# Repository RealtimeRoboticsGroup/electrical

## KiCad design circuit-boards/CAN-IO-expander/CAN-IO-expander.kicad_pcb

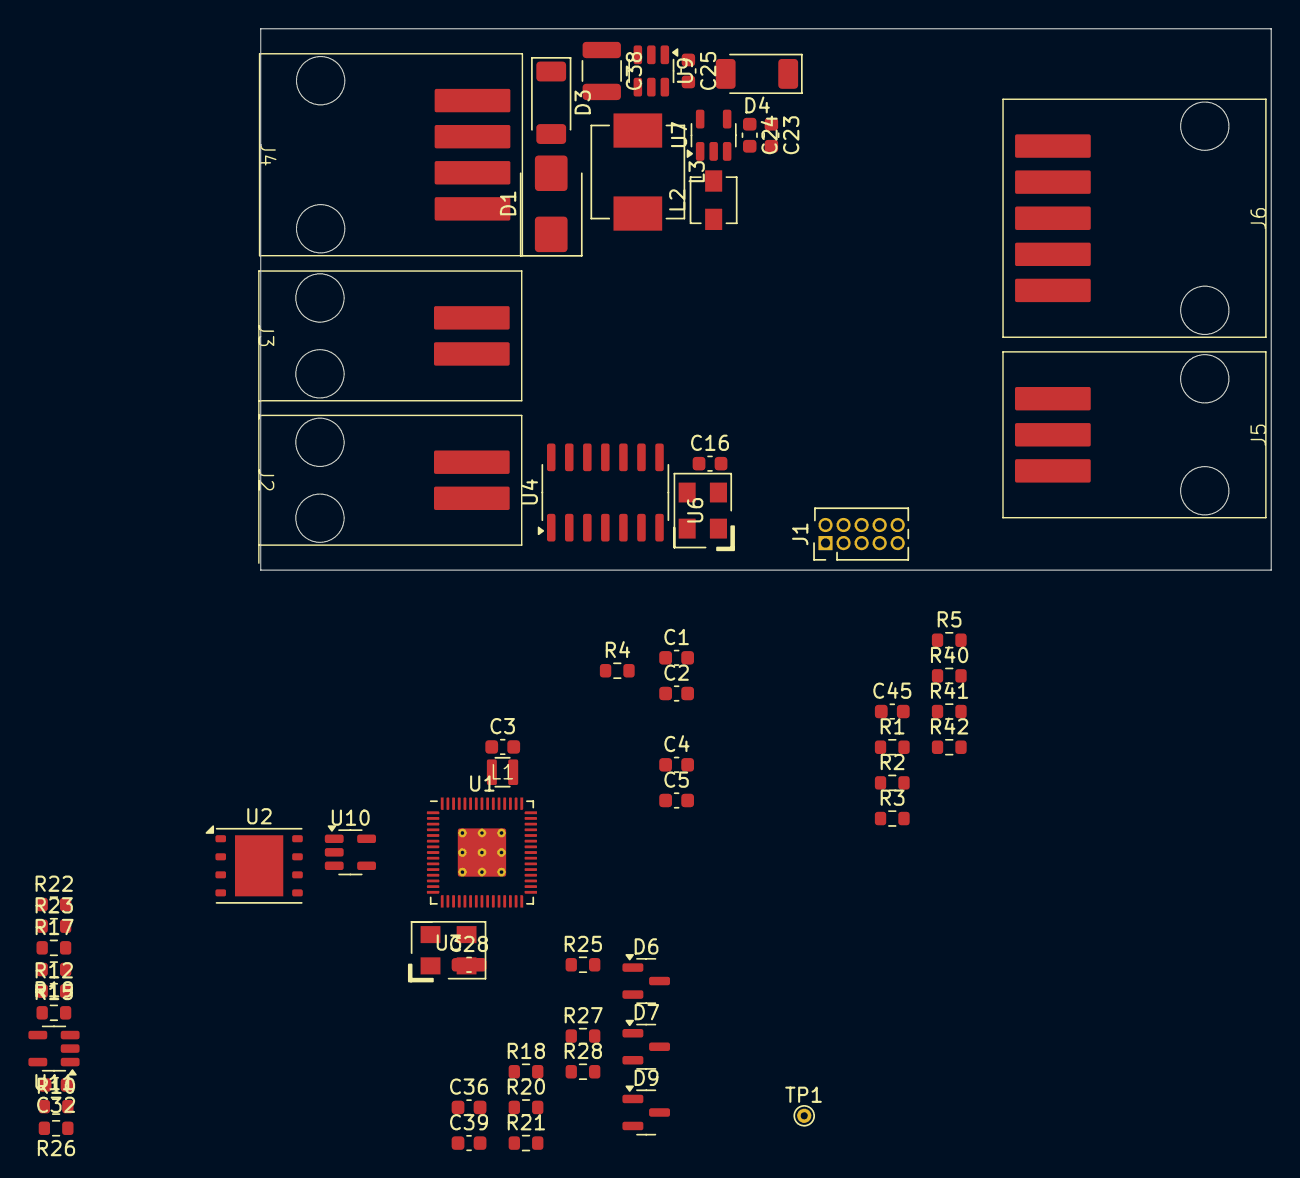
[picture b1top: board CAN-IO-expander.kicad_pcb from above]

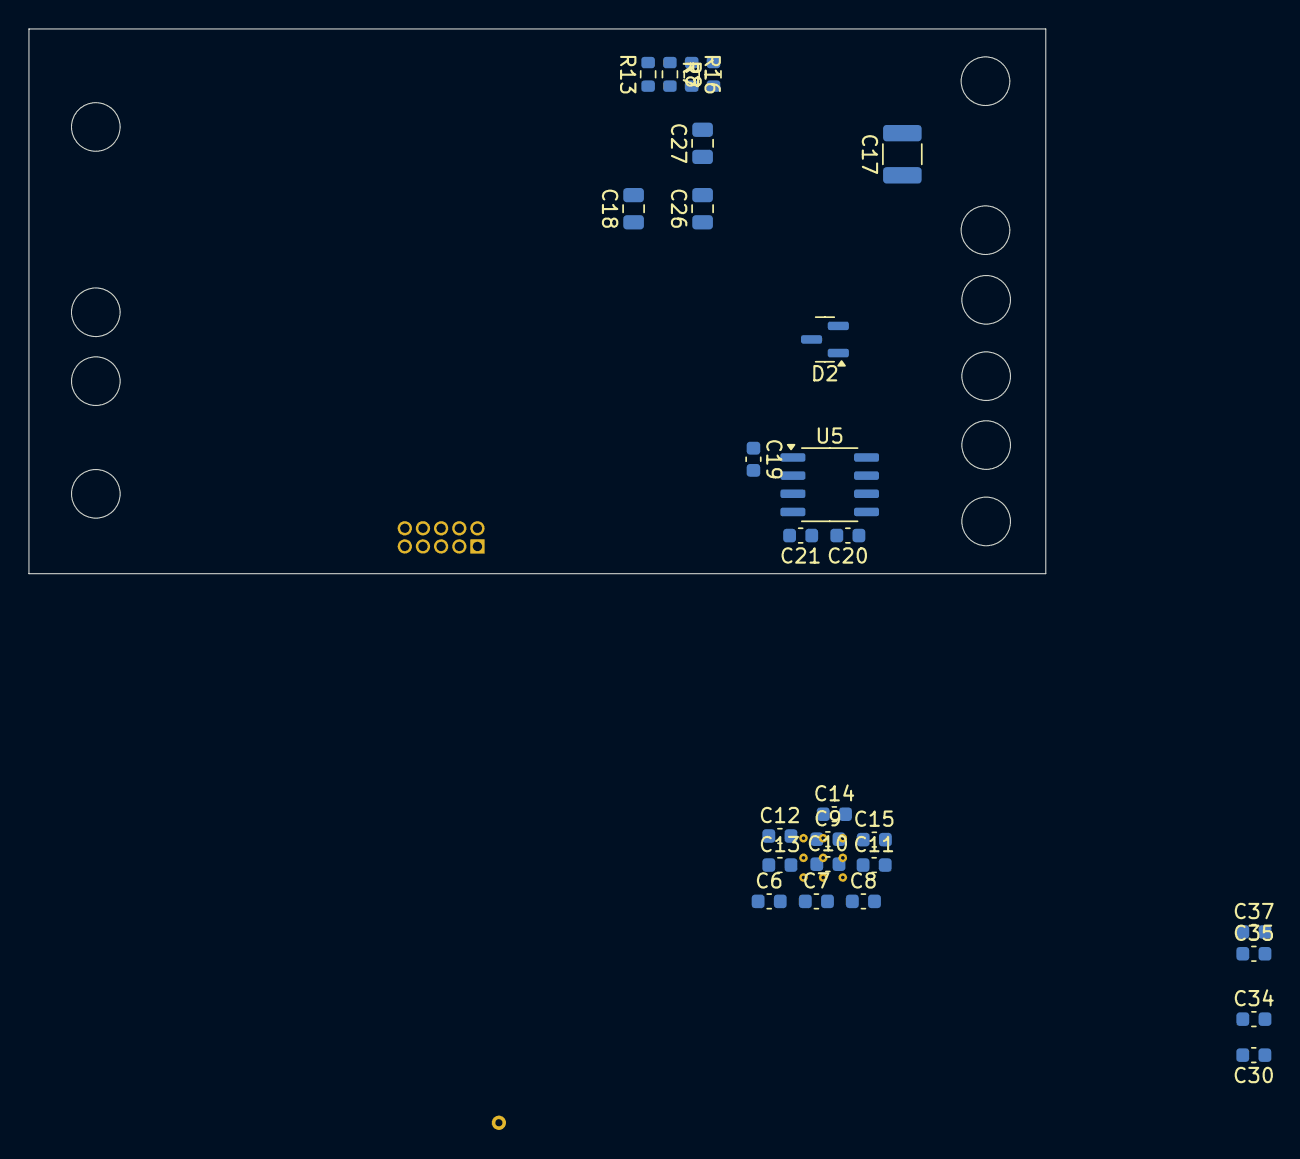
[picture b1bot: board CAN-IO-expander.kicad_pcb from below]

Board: 2 copper layers, 71.1 x 38.1 mm, 89 parts (27 on the bottom side), 63 nets, no tracks yet.

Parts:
C1, C2, C7, C8, C9, C10, C11, C12, C13, C14, C15, C16, C19, C20, C21, C25, C30, C45: 0.1uF-25V-10%-0603; C_0603_1608Metric
C3, C4, C5, C6: 4.7uF-16V-10%-0603; C_0603_1608Metric
C17, C38: 22uF-25V-10%-1210; C_1210_3225Metric
C18, C26, C27: 10uF-10%-10V-0805; C_0805_2012Metric
C23, C24: 22uF-20%-0603; C_0603_1608Metric
C28, C32, C34, C35, C36, C37, C39: 1nF-50V-5%-0603; C_0603_1608Metric
D1: 15V; D_SMB
D2: PESD1CAN; SOT-23
D3, D4: PMEG3020EP,115; D_SOD-128
D6, D7, D9: BAV199; SOT-23
J1: PROG; PinHeader_2x05_P1.27mm_Vertical
J2, J3: CAN1; Molex-70634-0036
J4: 12V; Molex-70634-0038
J5: POT; Molex-70634-0037
J6: ENCODER; Molex-70634-0039
L1: 3.3uH-20%-0806; L_Taiyo_Yuden_0806
L2: 2.2uH-20%-46mR; L_Vishay_IHLP-1212
L3: 8.2uH-20%-55mR; L_Vishay_IHLP-2525
R1, R5, R10, R12, R18, R20, R21: 1.00k-1%-0603; R_0603_1608Metric
R2, R3, R4: 27R0-1%-0603; R_0603_1608Metric
R7: 63.4k-1%-0603; R_0603_1608Metric
R8, R13: 20.0k-1%-0603; R_0603_1608Metric
R15, R17, R19, R23, R40, R41, R42: 2.00k-1%-0603; R_0603_1608Metric
R16, R22: 10.0k-1%-0603; R_0603_1608Metric
R25, R27, R28: 100R-1%-0603; R_0603_1608Metric
R26: 1.00M-1%-0603; R_0603_1608Metric
TP1: CLKO; TestPoint_THTPad_D1.0mm_Drill0.5mm
U1: RP2350_60QFN; RP2350-QFN-60-1EP_7x7_P0.4mm_EP3.4x3.4mm_ThermalVias
U2: W25Q128JVP; WSON-8-1EP_6x5mm_P1.27mm_EP3.4x4.3mm
U3: 12MHz; ECS-5032MV
U4: MCP2518FDT-H/SL; SO-14_3.9x8.65mm_P1.27mm
U5: MCP2558FD; SO-8_3.9x4.9mm_P1.27mm
U6: 4MHz; ECS-5032MV
U7: TPS613222ADBVR; SOT-23-5
U9: LMR54410FDBVR; SOT-23-6
U10: 24LC01BT-I/OT; SOT-23-5
U11: MCP6006UT-E/OT; SOT-23-5

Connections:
+1V1: C3.1, C6.1, C7.1, C8.1, L1.1, U1.6 (DVDD), U1.23 (DVDD), U1.39 (DVDD), U1.50 (VREG_FB)
+3V3: C1.1, C2.1, C4.1, C16.1, C18.1, C19.1, C20.1, C26.1, C27.1, C45.1, D6.2 (A), D7.2 (A), D9.2 (A), L2.1, L3.2, R2.1, R7.2, R40.2, R41.2, R42.2, U1.49 (VREG_VIN), U2.8 (VCC), U3.1 (EN), U3.4 (V_{DD}), U4.14 (VDD), U5.5 (V_{IO}), U6.1 (EN), U6.4 (V_{DD}), U10.4 (Vcc)
+5V: C21.1, C23.1, C24.1, C30.1, D4.2 (A), U5.3 (V_{DD}), U7.4 (VOUT), U11.5 (V+)
+5V_EXT: D4.1 (K), J5.2, J6.4, R19.2
/5V_ADC: C35.1, R17.2, R19.1, U1.42 (GPIO28_ADC2)
/AIN0: J5.3, R10.1, R26.2
/AIN0_ADC: C34.1, R12.2, R15.2, U1.40 (GPIO26_ADC0)
/CAN1_H: D2.2 (K1), J2.2, J3.2, U5.7 (CANH)
/CAN1_L: D2.1 (K1), J2.1, J3.1, U5.6 (CANL)
/CAN-FD/CANRX: U4.2 (RXCAN), U5.4 (RXD)
/CAN-FD/CANTX: U4.1 (TXCAN), U5.1 (TXD)
/CAN-FD/CLK: U4.6 (OSC1), U6.3 (OUT)
/DI00: D6.3 (K), R21.2, U1.18 (GPIO14)
/DI10: D7.3 (K), R20.2, U1.16 (GPIO12)
/DI20: D9.3 (K), R18.2, U1.19 (GPIO15), U1.28 (GPIO17)
/EEPROM_WP: R42.1, U1.14 (GPIO10), U10.5 (WP)
/I2C0_SCL: R40.1, U1.13 (GPIO9), U10.1 (SCL)
/I2C0_SDA: R41.1, U1.12 (GPIO8), U10.3 (SDA)
/PWM_IN0: J6.1, R25.1
/QA0: J6.3, R28.1
/QB0: J6.2, R27.1
/QSPI_D0: U1.57 (QSPI_SD0), U2.5 (DI/IO_{0})
/QSPI_D1: U1.59 (QSPI_SD1), U2.2 (DO/IO_{1})
/QSPI_D2: U1.58 (QSPI_SD2), U2.3 (~WP/IO_{2})
/QSPI_D3: U1.55 (QSPI_SD3), U2.7 (~HOLD/~RESET/IO_{3})
/QSPI_SCLK: U1.56 (QSPI_SCLK), U2.6 (CLK)
/SILENT: U1.10 (GPIO7), U5.8 (S)
/SPI0_RX: U1.2 (GPIO0), U4.12 (SDO)
/SPI0_SCK: U1.4 (GPIO2), U4.10 (SCK)
/SPI0_TX: U1.5 (GPIO3), U4.11 (SDI)
/SWCLK: J1.4, U1.24 (SWCLK)
/SWD: J1.6, U1.25 (SWD)
/USB_D+: J1.2, R3.2
/USB_D-: J1.1, R4.2
/VBAT_ADC: C37.1, R22.2, R23.2, U1.43 (GPIO29_ADC3)
/VREG_LX: L1.2, U1.48 (VREG_LX)
/V_{BAT}: C17.2, D1.2 (A2), D3.2 (A), J4.3, J4.4
/~CAN_INT: U1.7 (GPIO4), U4.4 (~INT)
/~CAN_RX_INT: U1.8 (GPIO5), U4.9 (~INT0/GPIO0/XSTBY)
/~CAN_TX_INT: U1.9 (GPIO6), U4.8 (~INT1/GPIO1)
/~QSPI_SS: R1.2, U1.60 (QSPI_SS), U2.1 (~CS)
/~RESET: J1.10, R5.1
/~SPI0_CS: U1.3 (GPIO1), U4.13 (~CS)
/~USB_BOOT: J1.8, R1.1
GND: C1.2, C2.2, C3.2, C4.2, C5.2, C6.2, C7.2, C8.2, C9.2, C10.2, C11.2, C12.2, C13.2, C14.2, C15.2, C16.2, C17.1, C18.2, C19.2, C20.2, C21.2, C23.2, C24.2, C26.2, C27.2, C28.2, C30.2, C32.2, C34.2, C35.2, C36.2, C37.2, C38.1, C39.2, C45.2, D1.1 (A1), D2.3 (KK), D6.1 (K), D7.1 (K), D9.1 (K), J1.5, J1.7, J1.9, J4.1, J4.2, J5.1, J6.5, R13.1, R15.1, R16.1, R17.1, R23.1, R26.1, U1.47 (VREG_PGND), U1.61 (GND), U2.4 (GND), U2.9 (EP), U3.2 (GND), U4.7 (VSS), U5.2 (V_{SS}), U6.2 (GND), U7.2 (GND), U7.3 (NC), U7.5 (NC), U9.2 (GND), U10.2 (Vss), U11.2 (V-)
unnamed: C28.1, R21.1, R28.2
unnamed: C36.1, R20.1, R27.2
unnamed: C39.1, R18.1, R25.2
unnamed: C38.2, D3.1 (K), R8.2, R22.1, U9.5 (VIN)
unnamed: C9.1, C10.1, C11.1, C12.1, C13.1, C14.1, C15.1, U1.1 (IOVDD), U1.11 (IOVDD), U1.20 (IOVDD), U1.30 (IOVDD), U1.38 (IOVDD), U1.44 (ADC_AVDD), U1.45 (IOVDD), U1.53 (USB_OTP_VDD), U1.54 (QSPI_IOVDD)
unnamed: R5.2, U1.26 (RUN)
unnamed: R4.1, U1.51 (USB_DM)
unnamed: R3.1, U1.52 (USB_DP)
unnamed: C5.1, R2.2, U1.46 (VREG_AVDD)
unnamed: U1.21 (XIN), U3.3 (OUT)
unnamed: TP1.1, U4.3 (CLKO/SOF)
unnamed: L2.2, U7.1 (SW)
unnamed: C25.1, U9.1 (CB)
unnamed: R8.1, R16.2, U9.4 (EN)
unnamed: R7.1, R13.2, U9.3 (FB)
unnamed: C25.2, L3.1, U9.6 (SW)
unnamed: C32.1, R10.2, U11.3 (+)
unnamed: R12.1, U11.1, U11.4 (-)

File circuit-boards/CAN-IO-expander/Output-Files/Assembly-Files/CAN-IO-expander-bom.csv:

"Reference","Value","DIST","DIST P/N","MFG","MFG P/N","Item","QUANTITY"
"C1,C2,C7-C16,C19-C21,C28-C37,C39-C45,J4-J7,R1-R5,R10-R12,R14,R15,R17-R21,R23-R42","0.1uF-25V-10%-0603,1.00M-1%-0603,1.00k-1%-0603,100R-1%-0603,1nF-50V-5%-0603,2.00k-1%-0603,27R0-1%-0603,Conn_01x03_Pin,Conn_01x06_Pin","","","","","1","71"
"C3-C6","4.7uF-16V-10%-0603","Digikey","CL10A475KO8NNNC","Samsung Electro-Mechanics","CL10A475KO8NNNC","2","4"
"C17,C38","22uF-25V-10%-1210","Digikey","1276-3369-1-ND","Samsung Electro-Mechanics","CL32A226KAJNNWE","3","2"
"C18,C26,C27","10uF-10%-10V-0805","Digikey","399-C0805C106K8PAC7800CT-ND","Kemet","C0805C106K8PAC7800","4","3"
"C22","330uF-35V-20%-10mm","Digikey","1189-35PZJ330M10X9-ND","Rubycon","35PZJ330M10X9","5","1"
"C23,C24","22uF-20%-0603","Digikey","445-9077-1-ND","TDK","C1608X5R1A226M080AC","6","2"
"C25","0.1uF-25V-10%-0603","Digikey","478-KGM15BR71E104KMCT-ND","Kyocera AVX","KGM15BR71E104KM","7","1"
"D1","15V","Digikey","F11544CT-ND","Littelfuse","SZ1SMB15CAT3G","8","1"
"D2","PESD1CAN","Digikey","1727-3817-1-ND","Nexperia","PESD1CAN,215","9","1"
"D3,D4","PMEG3020EP,115","Digikey","1727-5836-1-ND","Nexperia","PMEG3020EP,115","10","2"
"D5-D12","BAV199","Digikey","BAV199LT1GOSCT-ND","onsemi","BAV199LT1G","11","8"
"J2,J3","CAN1","Digikey","WM4175-ND","Molex","0705550036","12","2"
"J8","Power","Digikey","2946-2604-3102-ND","Wago","2604-3102","13","1"
"L1","3.3uH-20%-0806","Digikey","587-6083-1-ND","Taiyo Yuden","MAKK2016T3R3M","14","1"
"L2","2.2uH-20%-46mR","Digikey","541-1322-1-ND","Vishay","IHLP1212BZER2R2M11","15","1"
"L3","8.2uH-20%-55mR","Digikey","541-IHLP2525CZER8R2M1ACT-ND","Vishay","IHLP2525CZER8R2M1A","16","1"
"R7","63.4k-1%-0603","Digikey","311-63.4KHRCT-ND","Yageo","RC0603FR-0763K4L","17","1"
"R8,R13","20.0k-1%-0603","Digikey","311-20.0KHRCT-ND","Yageo","RC0603FR-0720KL","18","2"
"R16,R22","10.0k-1%-0603","Digikey","YAG1290CT-ND","Yageo","RC0603FR-0710KP","19","2"
"U1","RP2350_60QFN","Digikey","2648-SC1509CT-ND","Raspberry Pi","SC1509","20","1"
"U2","W25Q128JVP","Digikey","W25Q128JVPIQ-ND","Winbond Electronics","W25Q128JVPIQ","21","1"
"U3","12MHz","Digikey","XC3101CT-ND","ECS Inc","ECS-5032MV-120-CN-TR","22","1"
"U4","MCP2518FDT-H/SL","Digikey","MCP2518FDT-H/SLCT-ND","Microchip","MCP2518FDT-H/SL","23","1"
"U5","MCP2558FD","Digikey","MCP2558FD-H/SN-ND","Microchip","MCP2558FD-H/SN","24","1"
"U6","4MHz","Digikey","XC3114CT-ND","ECS Inc","ECS-5032MV-40-CN-TR","25","1"
"U7","TPS613222ADBVR","Digikey","296-50503-1-ND","Texas Instruments","TPS613222ADBVR","26","1"
"U8,U11","MCP6006UT-E/OT","Digikey","150-MCP6006UT-E/OTCT-ND","Microchip","MCP6006UT-E/OT","27","2"
"U9","LMR54410FDBVR","Digikey","296-LMR54410FDBVRCT-ND","Texas Instruments","LMR54410FDBVR","28","1"
"U10","24LC01BT-I/OT","Digikey","24LC01BT-I/OTCT-ND","Microchip","24LC01BT-I/OT","29","1"

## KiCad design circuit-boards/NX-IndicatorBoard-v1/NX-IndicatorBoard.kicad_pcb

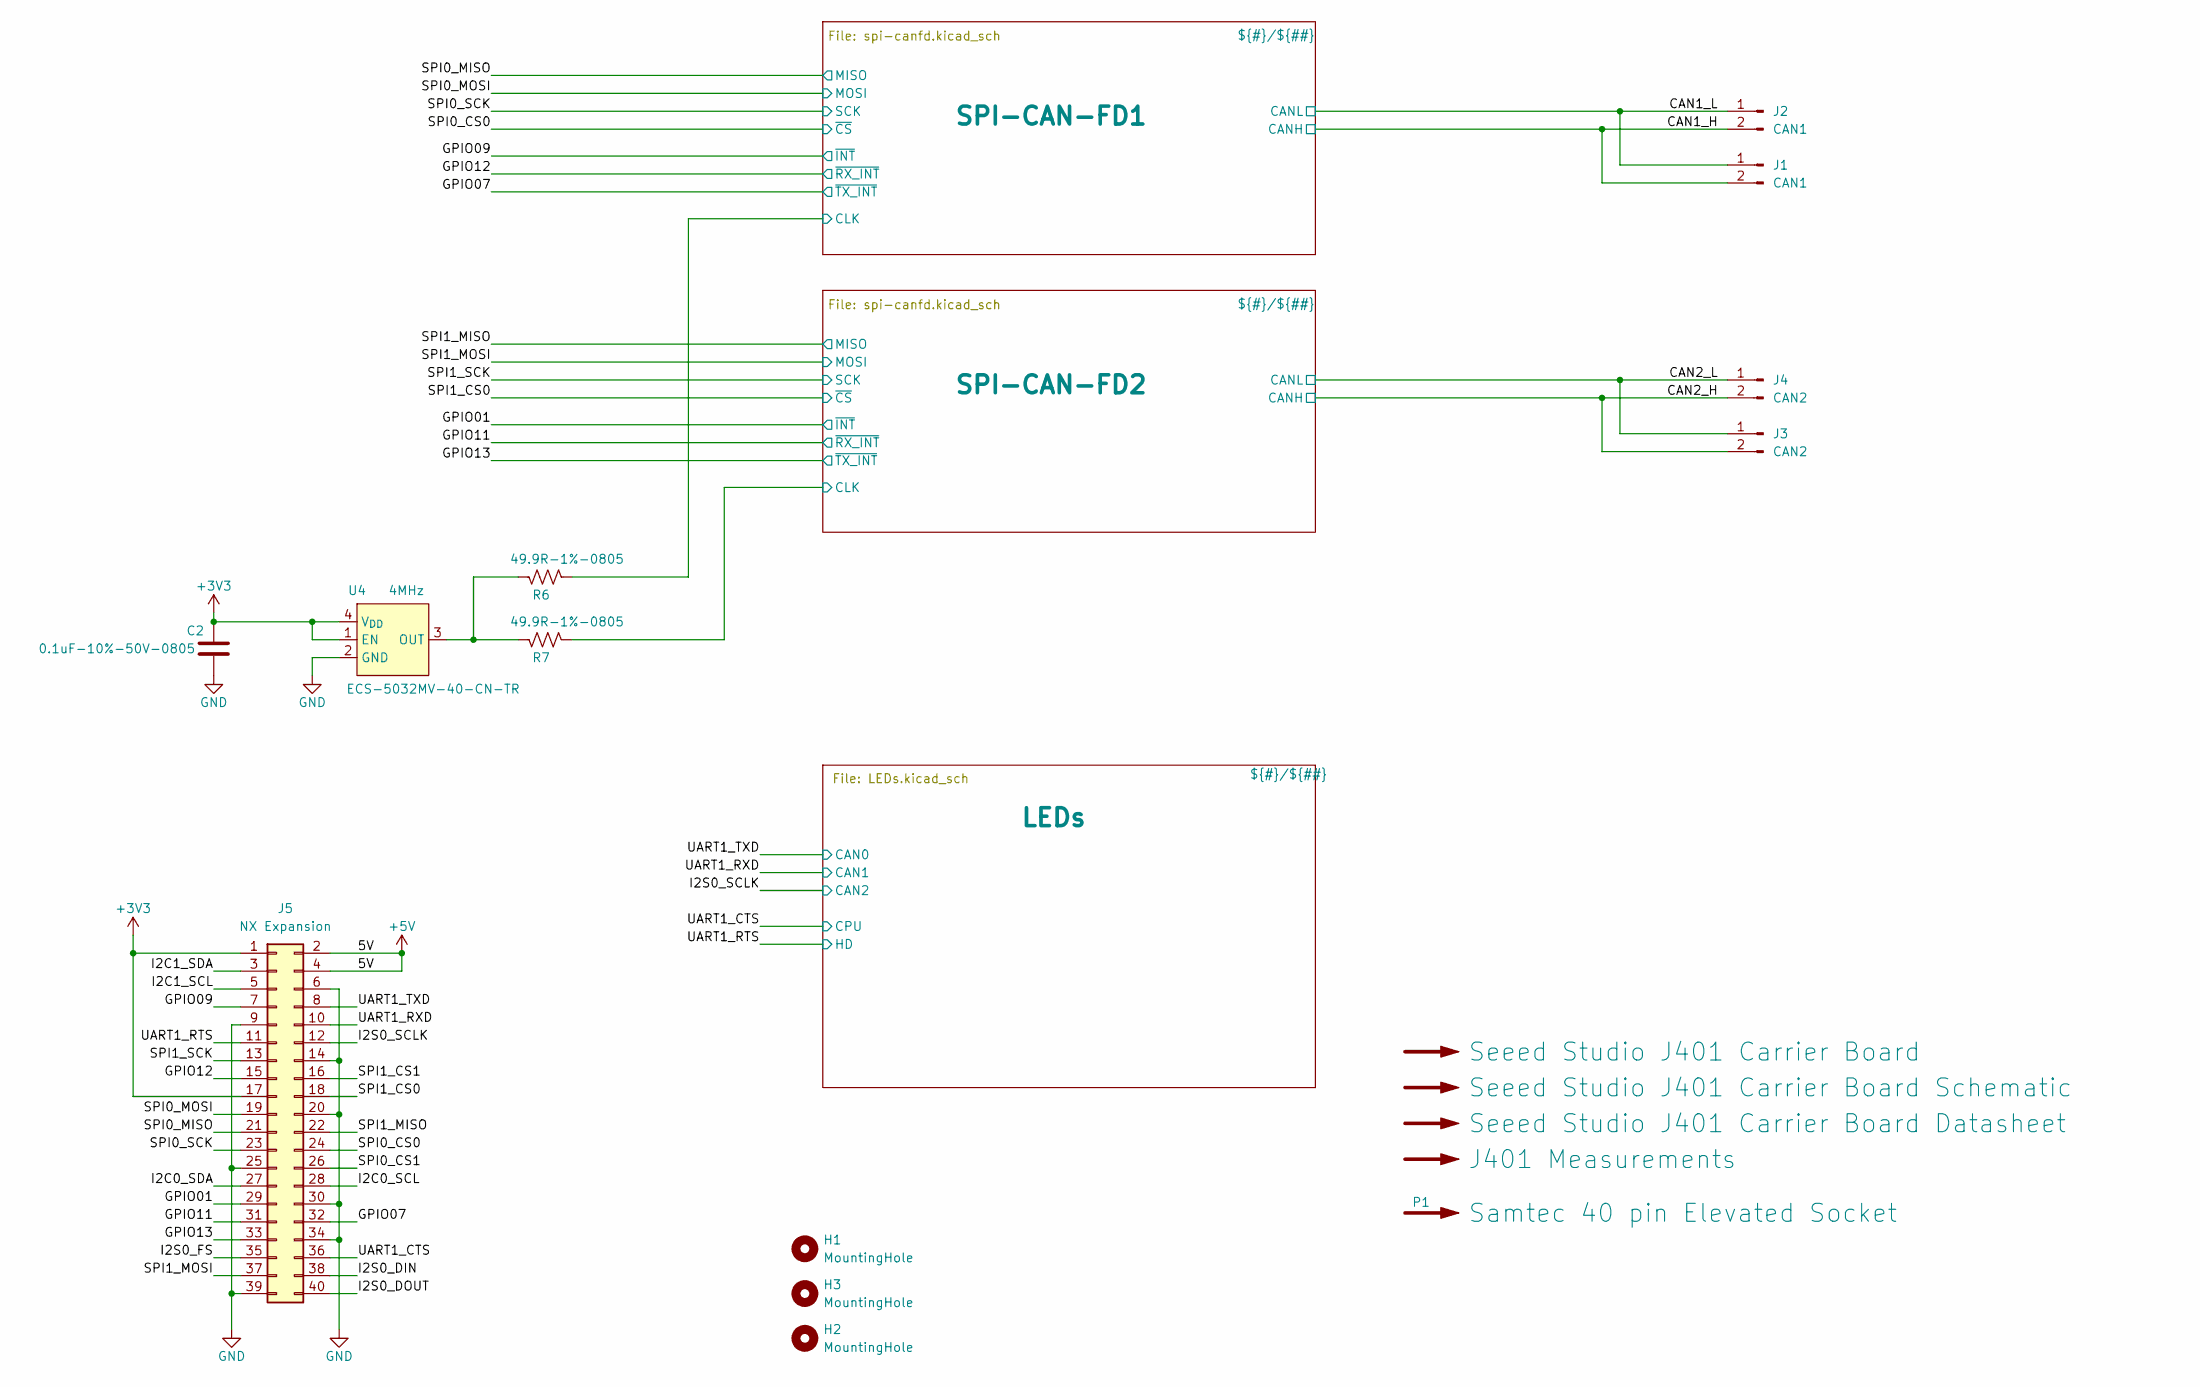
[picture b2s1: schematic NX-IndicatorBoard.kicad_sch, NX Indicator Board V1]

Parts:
C2: 0.1uF-10%-50V-0805; C_0805_2012Metric; MFG P/N CC0805KRX7R9BB104
H1, H2, H3: MountingHole; MountingHole_2.7mm_M2.5_Pad
J1, J2: CAN1; 70555-0001; MFG P/N 0705550036
J3, J4: CAN2; 70555-0001; MFG P/N 0705550036
J5: NX Expansion; M20-782045; MFG P/N M20-7812045
P1: Samtec 40 pin Elevated Socket; MFG P/N ESQ-120-34-G-D
R6, R7: 49.9R-1%-0805; R_0805_2012Metric; MFG P/N RC0805FR-0749R9L
U4: 4MHz; ECS-5032MV; MFG P/N ECS-5032MV-40-CN-TR

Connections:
+3V3: C2.1, J5.1, J5.17, U4.1 (EN), U4.4 (V_{DD}); also elsewhere on the board
+5V: J5.2, J5.4; also elsewhere on the board
/CAN1_H: J1.2, J2.2; also elsewhere on the board
/CAN1_L: J1.1, J2.1; also elsewhere on the board
/CAN2_H: J3.2, J4.2; also elsewhere on the board
/CAN2_L: J3.1, J4.1; also elsewhere on the board
/GPIO01: J5.29; also elsewhere on the board
/GPIO07: J5.32; also elsewhere on the board
/GPIO09: J5.7; also elsewhere on the board
/GPIO11: J5.31; also elsewhere on the board
/GPIO12: J5.15; also elsewhere on the board
/GPIO13: J5.33; also elsewhere on the board
/I2C0_SCL: J5.28
/I2C0_SDA: J5.27
/I2C1_SCL: J5.5
/I2C1_SDA: J5.3
/I2S0_DIN: J5.38
/I2S0_DOUT: J5.40
/I2S0_FS: J5.35
/I2S0_SCLK: J5.12; also elsewhere on the board
/SPI0_CS0: J5.24; also elsewhere on the board
/SPI0_CS1: J5.26
/SPI0_MISO: J5.21; also elsewhere on the board
/SPI0_MOSI: J5.19; also elsewhere on the board
/SPI0_SCK: J5.23; also elsewhere on the board
/SPI1_CS0: J5.18; also elsewhere on the board
/SPI1_CS1: J5.16
/SPI1_MISO: J5.22; also elsewhere on the board
/SPI1_MOSI: J5.37; also elsewhere on the board
/SPI1_SCK: J5.13; also elsewhere on the board
/SPI-CAN-FD1/CLK: R6.2; also elsewhere on the board
/SPI-CAN-FD2/CLK: R7.2; also elsewhere on the board
/UART1_CTS: J5.36; also elsewhere on the board
/UART1_RTS: J5.11; also elsewhere on the board
/UART1_RXD: J5.10; also elsewhere on the board
/UART1_TXD: J5.8; also elsewhere on the board
GND: C2.2, J5.6, J5.9, J5.14, J5.20, J5.25, J5.30, J5.34, J5.39, U4.2 (GND); also elsewhere on the board
unnamed: R6.1, R7.1, U4.3 (OUT)

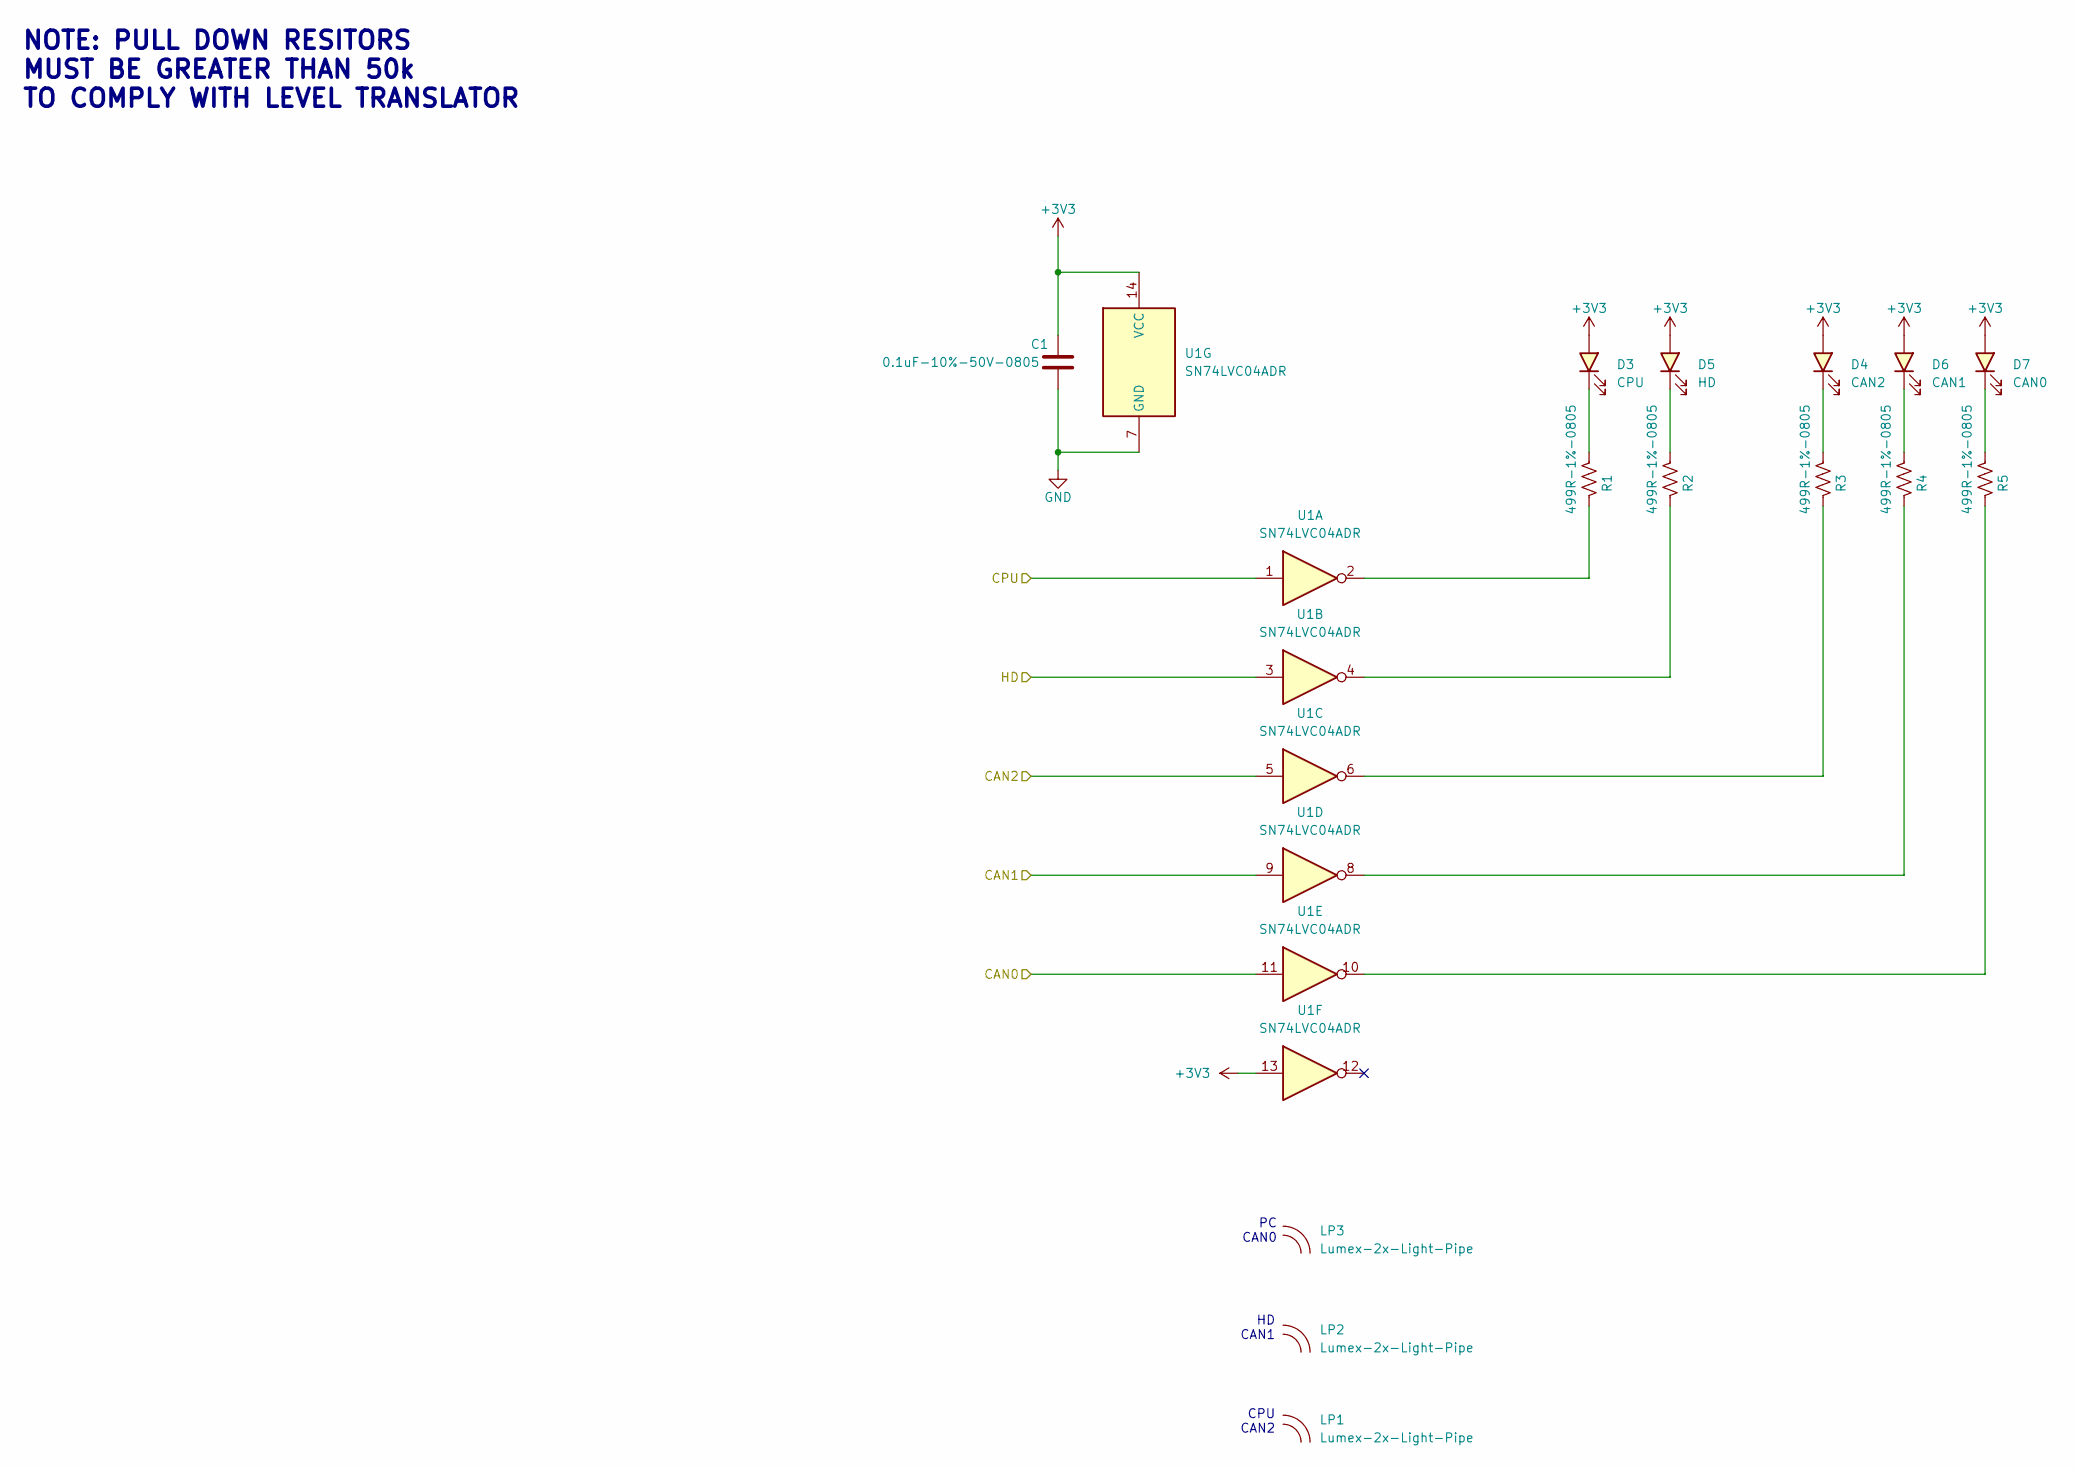
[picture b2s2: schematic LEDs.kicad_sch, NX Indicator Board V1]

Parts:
C1: 0.1uF-10%-50V-0805; C_0805_2012Metric; MFG P/N CC0805KRX7R9BB104
D3: CPU; LED_1206_3216Metric; MFG P/N QTLP650D4TR
D4: CAN2; LED_1206_3216Metric; MFG P/N QTLP650D4TR
D5: HD; LED_1206_3216Metric; MFG P/N QTLP650D4TR
D6: CAN1; LED_1206_3216Metric; MFG P/N QTLP650D4TR
D7: CAN0; LED_1206_3216Metric; MFG P/N QTLP650D4TR
LP1, LP2, LP3: Lumex-2x-Light-Pipe; Lumex-LPF-C012303S; MFG P/N LPF-C012303S
R1, R2, R3, R4, R5: 499R-1%-0805; R_0805_2012Metric; MFG P/N RC0805FR-07499RL
U1: SN74LVC04ADR; SO-14_3.9x8.65mm_P1.27mm; MFG P/N SN74LVC04ADR

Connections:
+3V3: C1.1, D3.2 (A), D4.2 (A), D5.2 (A), D6.2 (A), D7.2 (A), U1.13, U1.14 (VCC); also elsewhere on the board
/I2S0_SCLK: U1.5; also elsewhere on the board
/UART1_CTS: U1.1; also elsewhere on the board
/UART1_RTS: U1.3; also elsewhere on the board
/UART1_RXD: U1.9; also elsewhere on the board
/UART1_TXD: U1.11; also elsewhere on the board
GND: C1.2, U1.7 (GND); also elsewhere on the board
unnamed: D3.1 (K), R1.2
unnamed: D4.1 (K), R3.2
unnamed: D5.1 (K), R2.2
unnamed: D6.1 (K), R4.2
unnamed: D7.1 (K), R5.2
unnamed: R1.1, U1.2
unnamed: R2.1, U1.4
unnamed: R3.1, U1.6
unnamed: R4.1, U1.8
unnamed: R5.1, U1.10

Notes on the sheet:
CPU CAN2
PC CAN0
HD CAN1
NOTE: PULL DOWN RESITORS MUST BE GREATER THAN 50k TO COMPLY WITH LEVEL TRANSLATOR

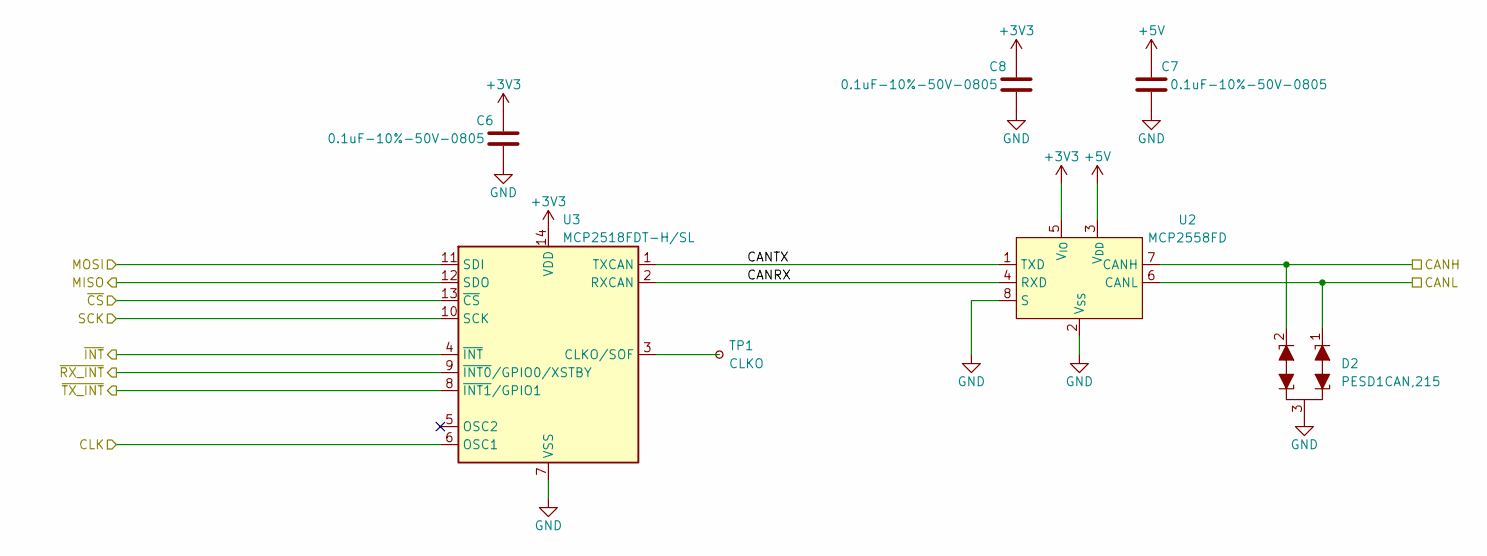
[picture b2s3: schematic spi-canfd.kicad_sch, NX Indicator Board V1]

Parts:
C6, C7, C8: 0.1uF-10%-50V-0805; C_0805_2012Metric; MFG P/N CC0805KRX7R9BB104
D2: PESD1CAN; SOT-23; MFG P/N PESD1CAN,215
TP1: CLKO; TestPoint_THTPad_D1.0mm_Drill0.5mm
U2: MCP2558FD; SO-8_3.9x4.9mm_P1.27mm; MFG P/N MCP2558FD-H/SN
U3: MCP2518FDT-H/SL; SO-14_3.9x8.65mm_P1.27mm; MFG P/N MCP2518FDT-H/SL

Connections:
+3V3: C6.1, C8.1, U2.5 (V_{IO}), U3.14 (VDD); also elsewhere on the board
+5V: C7.1, U2.3 (V_{DD}); also elsewhere on the board
/CAN1_H: D2.2 (K1), U2.7 (CANH); also elsewhere on the board
/CAN1_L: D2.1 (K1), U2.6 (CANL); also elsewhere on the board
/GPIO07: U3.8 (~INT1/GPIO1); also elsewhere on the board
/GPIO09: U3.4 (~INT); also elsewhere on the board
/GPIO12: U3.9 (~INT0/GPIO0/XSTBY); also elsewhere on the board
/SPI0_CS0: U3.13 (~CS); also elsewhere on the board
/SPI0_MISO: U3.12 (SDO); also elsewhere on the board
/SPI0_MOSI: U3.11 (SDI); also elsewhere on the board
/SPI0_SCK: U3.10 (SCK); also elsewhere on the board
/SPI-CAN-FD1/CANRX: U2.4 (RXD), U3.2 (RXCAN)
/SPI-CAN-FD1/CANTX: U2.1 (TXD), U3.1 (TXCAN)
/SPI-CAN-FD1/CLK: U3.6 (OSC1); also elsewhere on the board
GND: C6.2, C7.2, C8.2, D2.3 (KK), U2.2 (V_{SS}), U2.8 (S), U3.7 (VSS); also elsewhere on the board
unnamed: TP1.1, U3.3 (CLKO/SOF)

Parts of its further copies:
C3, C4, C5: 0.1uF-10%-50V-0805; C_0805_2012Metric; MFG P/N CC0805KRX7R9BB104
D1: PESD1CAN; SOT-23; MFG P/N PESD1CAN,215
TP2: CLKO; TestPoint_THTPad_D1.0mm_Drill0.5mm
U5: MCP2558FD; SO-8_3.9x4.9mm_P1.27mm; MFG P/N MCP2558FD-H/SN
U6: MCP2518FDT-H/SL; SO-14_3.9x8.65mm_P1.27mm; MFG P/N MCP2518FDT-H/SL

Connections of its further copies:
+3V3: C3.1, C5.1, U5.5 (V_{IO}), U6.14 (VDD); also elsewhere on the board
+5V: C4.1, U5.3 (V_{DD}); also elsewhere on the board
/CAN2_H: D1.2 (K1), U5.7 (CANH); also elsewhere on the board
/CAN2_L: D1.1 (K1), U5.6 (CANL); also elsewhere on the board
/GPIO01: U6.4 (~INT); also elsewhere on the board
/GPIO11: U6.9 (~INT0/GPIO0/XSTBY); also elsewhere on the board
/GPIO13: U6.8 (~INT1/GPIO1); also elsewhere on the board
/SPI1_CS0: U6.13 (~CS); also elsewhere on the board
/SPI1_MISO: U6.12 (SDO); also elsewhere on the board
/SPI1_MOSI: U6.11 (SDI); also elsewhere on the board
/SPI1_SCK: U6.10 (SCK); also elsewhere on the board
/SPI-CAN-FD2/CANRX: U5.4 (RXD), U6.2 (RXCAN)
/SPI-CAN-FD2/CANTX: U5.1 (TXD), U6.1 (TXCAN)
/SPI-CAN-FD2/CLK: U6.6 (OSC1); also elsewhere on the board
GND: C3.2, C4.2, C5.2, D1.3 (KK), U5.2 (V_{SS}), U5.8 (S), U6.7 (VSS); also elsewhere on the board
unnamed: TP2.1, U6.3 (CLKO/SOF)

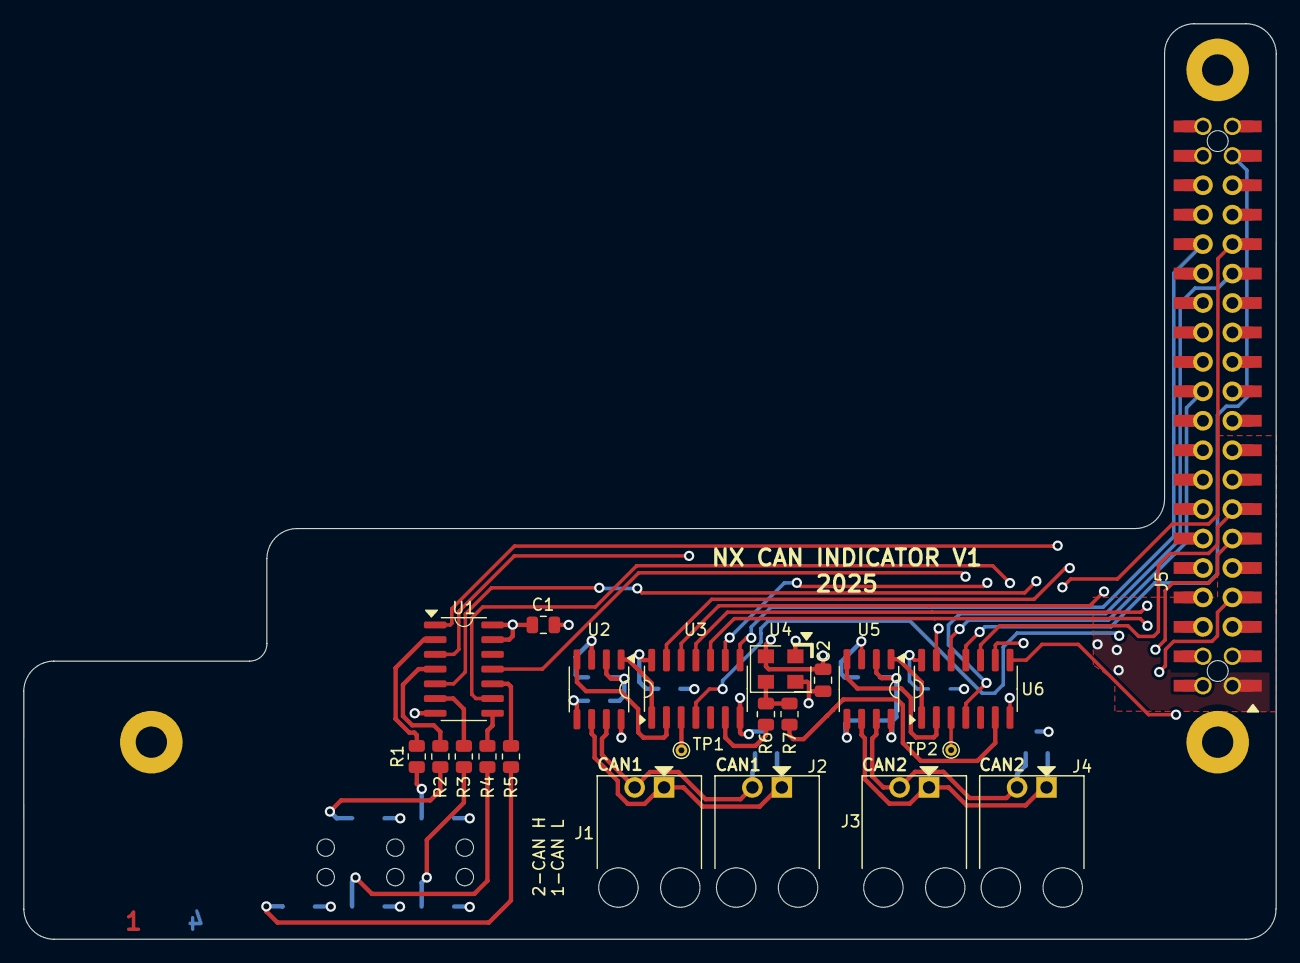
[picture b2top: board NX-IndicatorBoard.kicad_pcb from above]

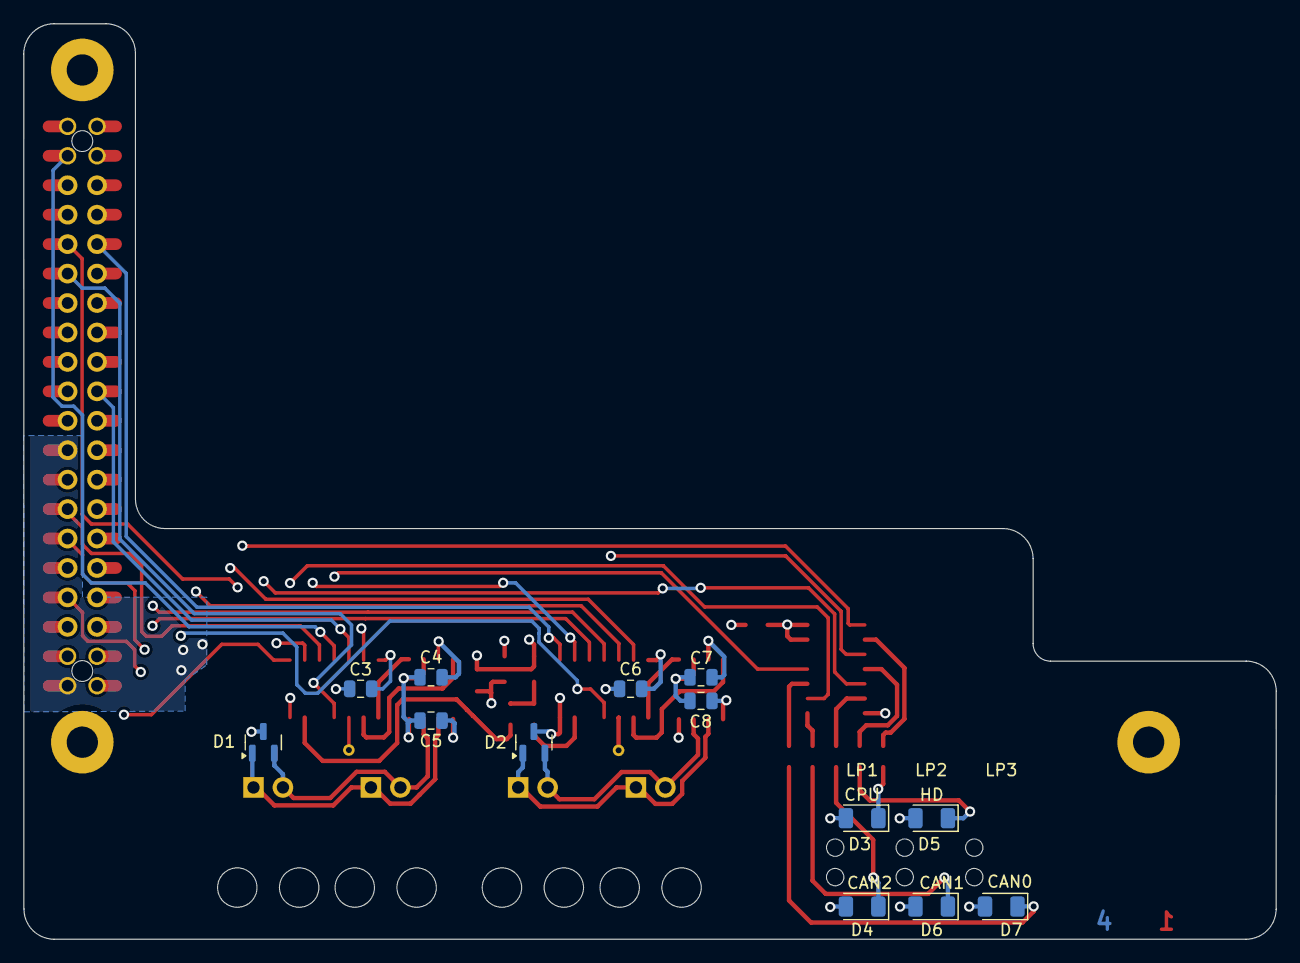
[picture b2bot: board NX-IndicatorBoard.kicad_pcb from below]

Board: 4 copper layers, 108.1 x 79.0 mm, 41 parts (16 on the bottom side), 45 nets.

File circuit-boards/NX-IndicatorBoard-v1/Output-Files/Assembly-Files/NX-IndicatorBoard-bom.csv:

"Reference","Value","DIST","DIST P/N","MFG","MFG P/N","Item","QUANTITY"
"C1-C8","0.1uF-10%-50V-0805","Digikey","311-1140-1-ND","YAGEO","CC0805KRX7R9BB104","1","8"
"D1,D2","PESD1CAN","Digikey","1727-3817-1-ND","Nexperia","PESD1CAN,215","2","2"
"D3-D7","CAN0,CAN1,CAN2,CPU,HD","Digikey","1080-1419-1-ND","Everlight Electronics","QTLP650D4TR","3","5"
"J1-J4","CAN1,CAN2","Digikey","WM4175-ND","Molex","0705550036","4","4"
"J5","NX Expansion","Digikey","952-3218-ND","Harwin","M20-7812045","5","1"
"LP1-LP3","Lumex-2x-Light-Pipe","Digikey","67-1850-ND","Lumex","LPF-C012303S","6","3"
"P1","Samtec 40 pin Elevated Socket","Digikey","SAM9319-ND","Samtec","ESQ-120-34-G-D","7","1"
"R1-R5","499R-1%-0805","Digikey","311-499CRCT-ND","YAGEO","RC0805FR-07499RL","8","5"
"R6,R7","49.9R-1%-0805","Digikey","311-49.9CRCT-ND","YAGEO","RC0805FR-0749R9L","9","2"
"U1","SN74LVC04ADR","Digikey","296-1218-1-ND","Texas Instruments","SN74LVC04ADR","10","1"
"U2,U5","MCP2558FD","Digikey","MCP2558FD-H/SN-ND","Microchip","MCP2558FD-H/SN","11","2"
"U3,U6","MCP2518FDT-H/SL","Digikey","MCP2518FDT-H/SLCT-ND","Microchip","MCP2518FDT-H/SL","12","2"
"U4","4MHz","Digikey","XC3114CT-ND","ECS Inc","ECS-5032MV-40-CN-TR","13","1"

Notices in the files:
circuit-boards/NX-J401-Adapter-v4/NX-J401-Adapter.kicad_pcb:
(C)2025
parts and their libraries:
Copyright 2021 Accelerated Designs. All rights reserved.
